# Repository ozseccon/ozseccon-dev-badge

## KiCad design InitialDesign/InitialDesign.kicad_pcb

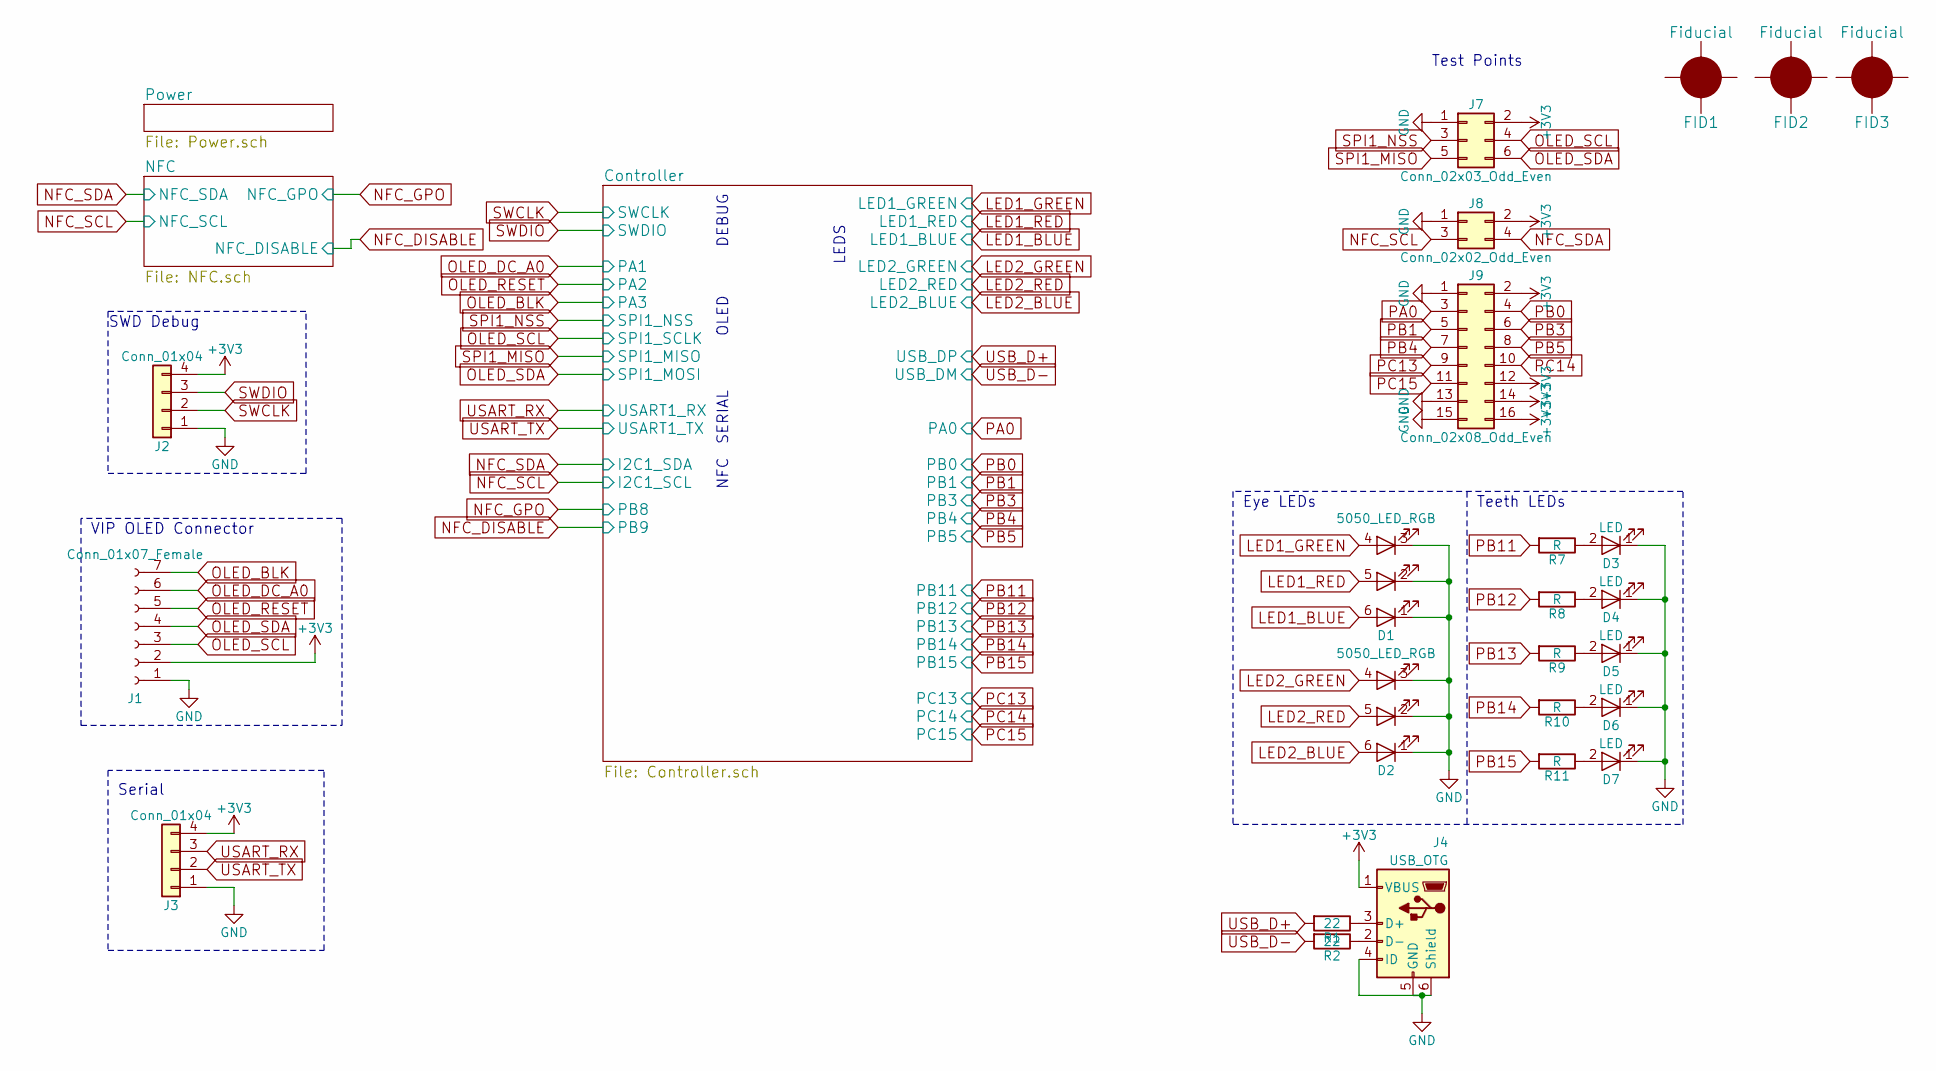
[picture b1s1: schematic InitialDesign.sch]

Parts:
D1, D2: 5050_LED_RGB; LED_RGB_5050-6
D3, D4, D5, D6, D7: LED; LED_1206
FID1, FID2, FID3: Fiducial; Fiducial_1.5mm_Dia_2.54mm_Outer_CopperTop
J1: Conn_01x07_Female; Socket_Strip_Straight_1x07_Pitch2.54mm
J2, J3: Conn_01x04; Pin_Header_Straight_1x04_Pitch2.54mm
J4: USB_OTG; USB_Micro-B
J7: Conn_02x03_Odd_Even; Pin_Header_Straight_2x03_Pitch2.54mm
J8: Conn_02x02_Odd_Even; Pin_Header_Straight_2x02_Pitch2.54mm
J9: Conn_02x08_Odd_Even; Pin_Header_Straight_2x08_Pitch2.54mm
R1, R2: 22; R_0805
R7, R8, R9, R10, R11: R; R_0805

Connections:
GND: D1.1 (K_BLUE), D1.2 (K_RED), D1.3 (K_GREEN), D2.1 (K_BLUE), D2.2 (K_RED), D2.3 (K_GREEN), D3.1 (K), D4.1 (K), D5.1 (K), D6.1 (K), D7.1 (K), J1.1, J2.1, J3.1, J4.4 (ID), J4.5 (GND), J4.6 (Shield), J7.1, J8.1, J9.1, J9.13, J9.15; also elsewhere on the board
LED1_BLUE: D1.6 (BLUE_A); also elsewhere on the board
LED1_GREEN: D1.4 (GREEN_A); also elsewhere on the board
LED1_RED: D1.5 (A_RED); also elsewhere on the board
LED2_BLUE: D2.6 (BLUE_A); also elsewhere on the board
LED2_GREEN: D2.4 (GREEN_A); also elsewhere on the board
LED2_RED: D2.5 (A_RED); also elsewhere on the board
NFC_SCL: J8.3; also elsewhere on the board
NFC_SDA: J8.4; also elsewhere on the board
unnamed: D3.2 (A), R7.1
unnamed: D4.2 (A), R8.1
unnamed: D5.2 (A), R9.1
unnamed: D6.2 (A), R10.1
unnamed: D7.2 (A), R11.1
unnamed: J4.2 (D-), R2.1
unnamed: J4.3 (D+), R1.1
OLED_BLK: J1.7; also elsewhere on the board
OLED_DC_A0: J1.6; also elsewhere on the board
OLED_RESET: J1.5; also elsewhere on the board
OLED_SCL: J1.3, J7.4; also elsewhere on the board
OLED_SDA: J1.4, J7.6; also elsewhere on the board
PA0: J9.3; also elsewhere on the board
PB0: J9.4; also elsewhere on the board
PB1: J9.5; also elsewhere on the board
PB3: J9.6; also elsewhere on the board
PB4: J9.7; also elsewhere on the board
PB5: J9.8; also elsewhere on the board
PB11: R7.2; also elsewhere on the board
PB12: R8.2; also elsewhere on the board
PB13: R9.2; also elsewhere on the board
PB14: R10.2; also elsewhere on the board
PB15: R11.2; also elsewhere on the board
PC13: J9.9; also elsewhere on the board
PC14: J9.10; also elsewhere on the board
PC15: J9.11; also elsewhere on the board
SPI1_MISO: J7.5; also elsewhere on the board
SPI1_NSS: J7.3; also elsewhere on the board
SWCLK: J2.2; also elsewhere on the board
SWDIO: J2.3; also elsewhere on the board
USART_RX: J3.3; also elsewhere on the board
USART_TX: J3.2; also elsewhere on the board
USB_D+: R1.2; also elsewhere on the board
USB_D-: R2.2; also elsewhere on the board

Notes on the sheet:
SWD Debug
VIP OLED Connector
Serial
DEBUG
OLED
SERIAL
NFC
LEDS
Teeth LEDs
Test Points
Eye LEDs

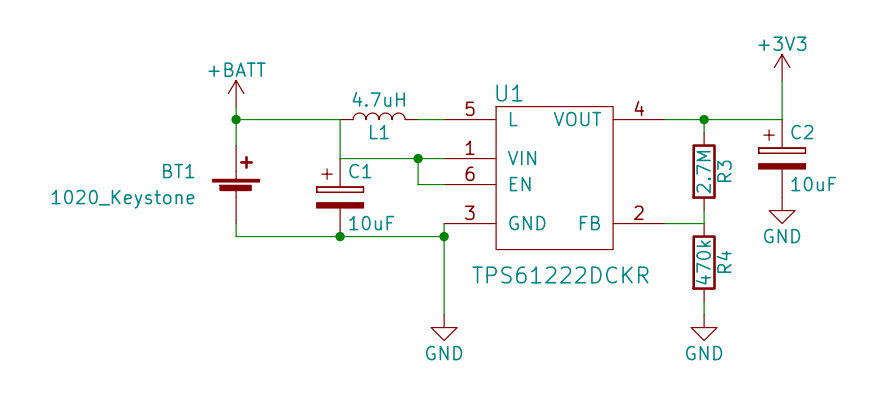
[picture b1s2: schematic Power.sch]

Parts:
BT1: 1020_Keystone; Keystone_2466_1xAAA
C1, C2: 10uF; CP_Elec_4x5.3
L1: 4.7uH; L_Taiyo-Yuden_NR-30xx
R3: 2.7M; R_0805
R4: 470k; R_0805
U1: TPS61222DCKR; SC-70-6

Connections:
+BATT: BT1.1 (+), C1.1, L1.1, U1.1 (VIN), U1.6 (EN)
GND: BT1.2 (-), C1.2, C2.2, R4.2, U1.3 (GND); also elsewhere on the board
unnamed: L1.2, U1.5 (L)
unnamed: R3.2, R4.1, U1.2 (FB)

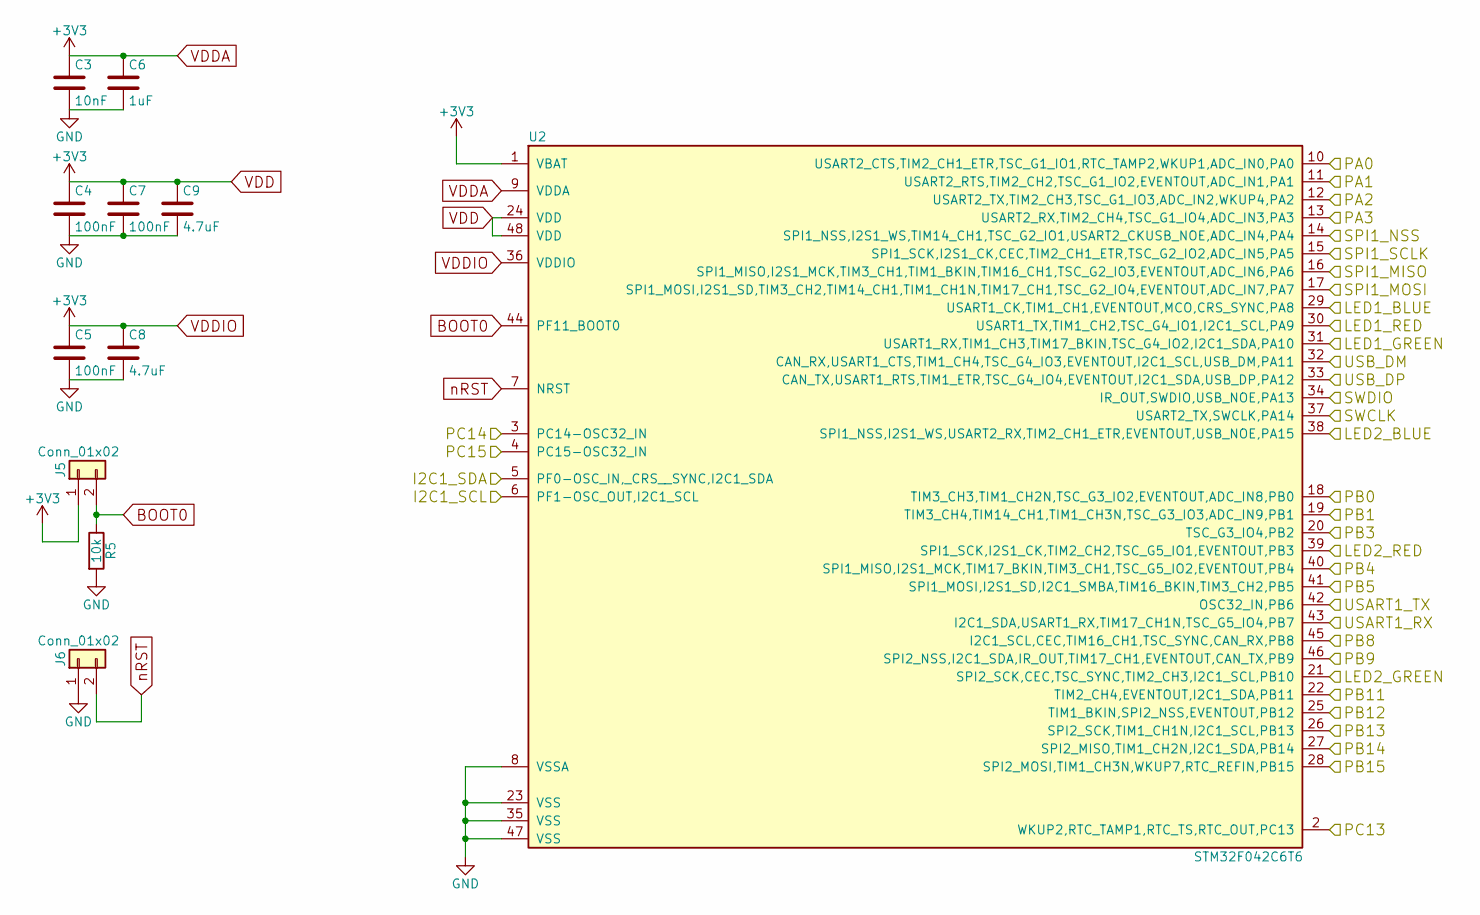
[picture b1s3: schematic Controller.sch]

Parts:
C3: 10nF; C_0805
C4, C5, C7: 100nF; C_0805
C6: 1uF; C_0805
C8, C9: 4.7uF; C_0805
J5, J6: Conn_01x02; Pin_Header_Straight_1x02_Pitch2.54mm
R5: 10k; R_0805
U2: STM32F042C6T6; LQFP-48_7x7mm_Pitch0.5mm

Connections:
BOOT0: J5.2, R5.1, U2.44 (PF11_BOOT0)
GND: C3.2, C4.2, C5.2, C6.2, C7.2, C8.2, C9.2, J6.1, R5.2, U2.8 (VSSA), U2.23 (VSS), U2.35 (VSS), U2.47 (VSS); also elsewhere on the board
LED1_BLUE: U2.29 (USART1_CK,TIM1_CH1,EVENTOUT,MCO,CRS_SYN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); also elsewhere on the board
LED1_GREEN: U2.31 (USART1_RX,TIM1_CH3,TIM17_BKIN,TSC_G4_IO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); also elsewhere on the board
LED1_RED: U2.30 (USART1_TX,TIM1_CH2,TSC_G4_IO1,I2C1_SCL,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); also elsewhere on the board
LED2_BLUE: U2.38 (SPI1_NSS,I2S1_WS,USART2_RX,TIM2_CH1_ETR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); also elsewhere on the board
LED2_GREEN: U2.21 (SPI2_SCK,CEC,TSC_SYNC,TIM2_CH3,I2C1_SCL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); also elsewhere on the board
LED2_RED: U2.39 (SPI1_SCK,I2S1_CK,TIM2_CH2,TSC_G5_IO1,EV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); also elsewhere on the board
NFC_DISABLE: U2.46 (SPI2_NSS,I2C1_SDA,IR_OUT,TIM17_CH1,EVEN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); also elsewhere on the board
NFC_GPO: U2.45 (I2C1_SCL,CEC,TIM16_CH1,TSC_SYNC,CAN_RX,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); also elsewhere on the board
NFC_SCL: U2.6 (PF1-OSC_OUT,I2C1_SCL); also elsewhere on the board
NFC_SDA: U2.5 (PF0-OSC_IN,_CRS__SYNC,I2C1_SDA); also elsewhere on the board
OLED_BLK: U2.13 (USART2_RX,TIM2_CH4,TSC_G1_IO4,ADC_IN3,P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); also elsewhere on the board
OLED_DC_A0: U2.11 (USART2_RTS,TIM2_CH2,TSC_G1_IO2,EVENTOUT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); also elsewhere on the board
OLED_RESET: U2.12 (USART2_TX,TIM2_CH3,TSC_G1_IO3,ADC_IN2,W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); also elsewhere on the board
OLED_SCL: U2.15 (SPI1_SCK,I2S1_CK,CEC,TIM2_CH1_ETR,TSC_G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); also elsewhere on the board
OLED_SDA: U2.17 (SPI1_MOSI,I2S1_SD,TIM3_CH2,TIM14_CH1,TI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); also elsewhere on the board
PA0: U2.10 (USART2_CTS,TIM2_CH1_ETR,TSC_G1_IO1,RTC_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); also elsewhere on the board
PB0: U2.18 (TIM3_CH3,TIM1_CH2N,TSC_G3_IO2,EVENTOUT,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); also elsewhere on the board
PB1: U2.19 (TIM3_CH4,TIM14_CH1,TIM1_CH3N,TSC_G3_IO3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); also elsewhere on the board
PB3: U2.20 (TSC_G3_IO4,PB2); also elsewhere on the board
PB4: U2.40 (SPI1_MISO,I2S1_MCK,TIM17_BKIN,TIM3_CH1,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); also elsewhere on the board
PB5: U2.41 (SPI1_MOSI,I2S1_SD,I2C1_SMBA,TIM16_BKIN,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); also elsewhere on the board
PB11: U2.22 (TIM2_CH4,EVENTOUT,I2C1_SDA,PB11); also elsewhere on the board
PB12: U2.25 (TIM1_BKIN,SPI2_NSS,EVENTOUT,PB12); also elsewhere on the board
PB13: U2.26 (SPI2_SCK,TIM1_CH1N,I2C1_SCL,PB13); also elsewhere on the board
PB14: U2.27 (SPI2_MISO,TIM1_CH2N,I2C1_SDA,PB14); also elsewhere on the board
PB15: U2.28 (SPI2_MOSI,TIM1_CH3N,WKUP7,RTC_REFIN,PB15); also elsewhere on the board
PC13: U2.2 (WKUP2,RTC_TAMP1,RTC_TS,RTC_OUT,PC13); also elsewhere on the board
PC14: U2.3 (PC14-OSC32_IN); also elsewhere on the board
PC15: U2.4 (PC15-OSC32_IN); also elsewhere on the board
SPI1_MISO: U2.16 (SPI1_MISO,I2S1_MCK,TIM3_CH1,TIM1_BKIN,T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); also elsewhere on the board
SPI1_NSS: U2.14 (SPI1_NSS,I2S1_WS,TIM14_CH1,TSC_G2_IO1,U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); also elsewhere on the board
SWCLK: U2.37 (USART2_TX,SWCLK,PA14); also elsewhere on the board
SWDIO: U2.34 (IR_OUT,SWDIO,USB_NOE,PA13); also elsewhere on the board
USART_RX: U2.43 (I2C1_SDA,USART1_RX,TIM17_CH1N,TSC_G5_IO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); also elsewhere on the board
USART_TX: U2.42 (OSC32_IN,PB6); also elsewhere on the board
USB_D+: U2.33 (CAN_TX,USART1_RTS,TIM1_ETR,TSC_G4_IO4,E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); also elsewhere on the board
USB_D-: U2.32 (CAN_RX,USART1_CTS,TIM1_CH4,TSC_G4_IO3,E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); also elsewhere on the board
nRST: J6.2, U2.7 (NRST)

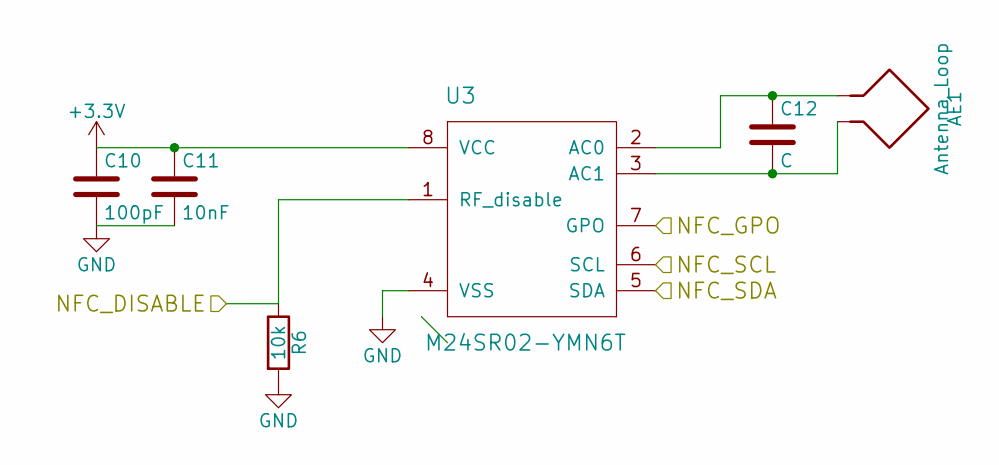
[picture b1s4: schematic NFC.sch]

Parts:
AE1: Antenna_Loop; NFC_Antenna
C10: 100pF; C_0805
C11: 10nF; C_0805
C12: C; C_0805
R6: 10k; R_0805
U3: M24SR02-YMN6T; SO-8_5.3x6.2mm_Pitch1.27mm

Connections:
GND: C10.2, C11.2, R6.2, U3.4 (VSS); also elsewhere on the board
NFC_DISABLE: R6.1, U3.1 (RF_disable); also elsewhere on the board
NFC_GPO: U3.7 (GPO); also elsewhere on the board
NFC_SCL: U3.6 (SCL); also elsewhere on the board
NFC_SDA: U3.5 (SDA); also elsewhere on the board
unnamed: AE1.1, C12.1, U3.2 (AC0)
unnamed: AE1.2, C12.2, U3.3 (AC1)

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
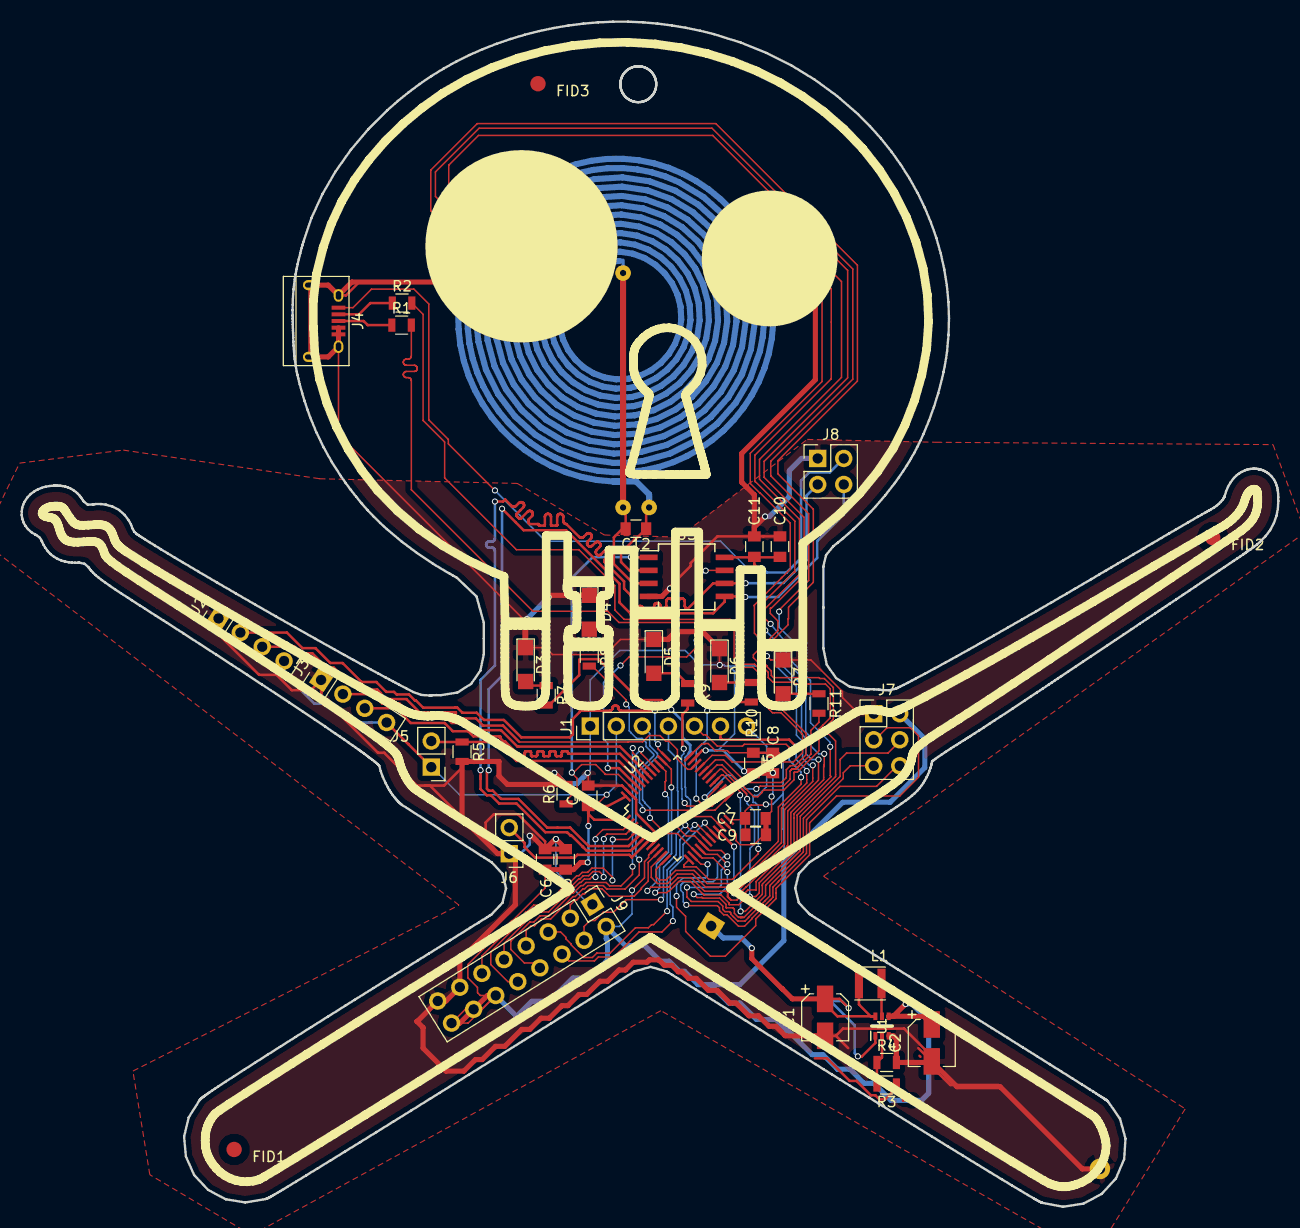
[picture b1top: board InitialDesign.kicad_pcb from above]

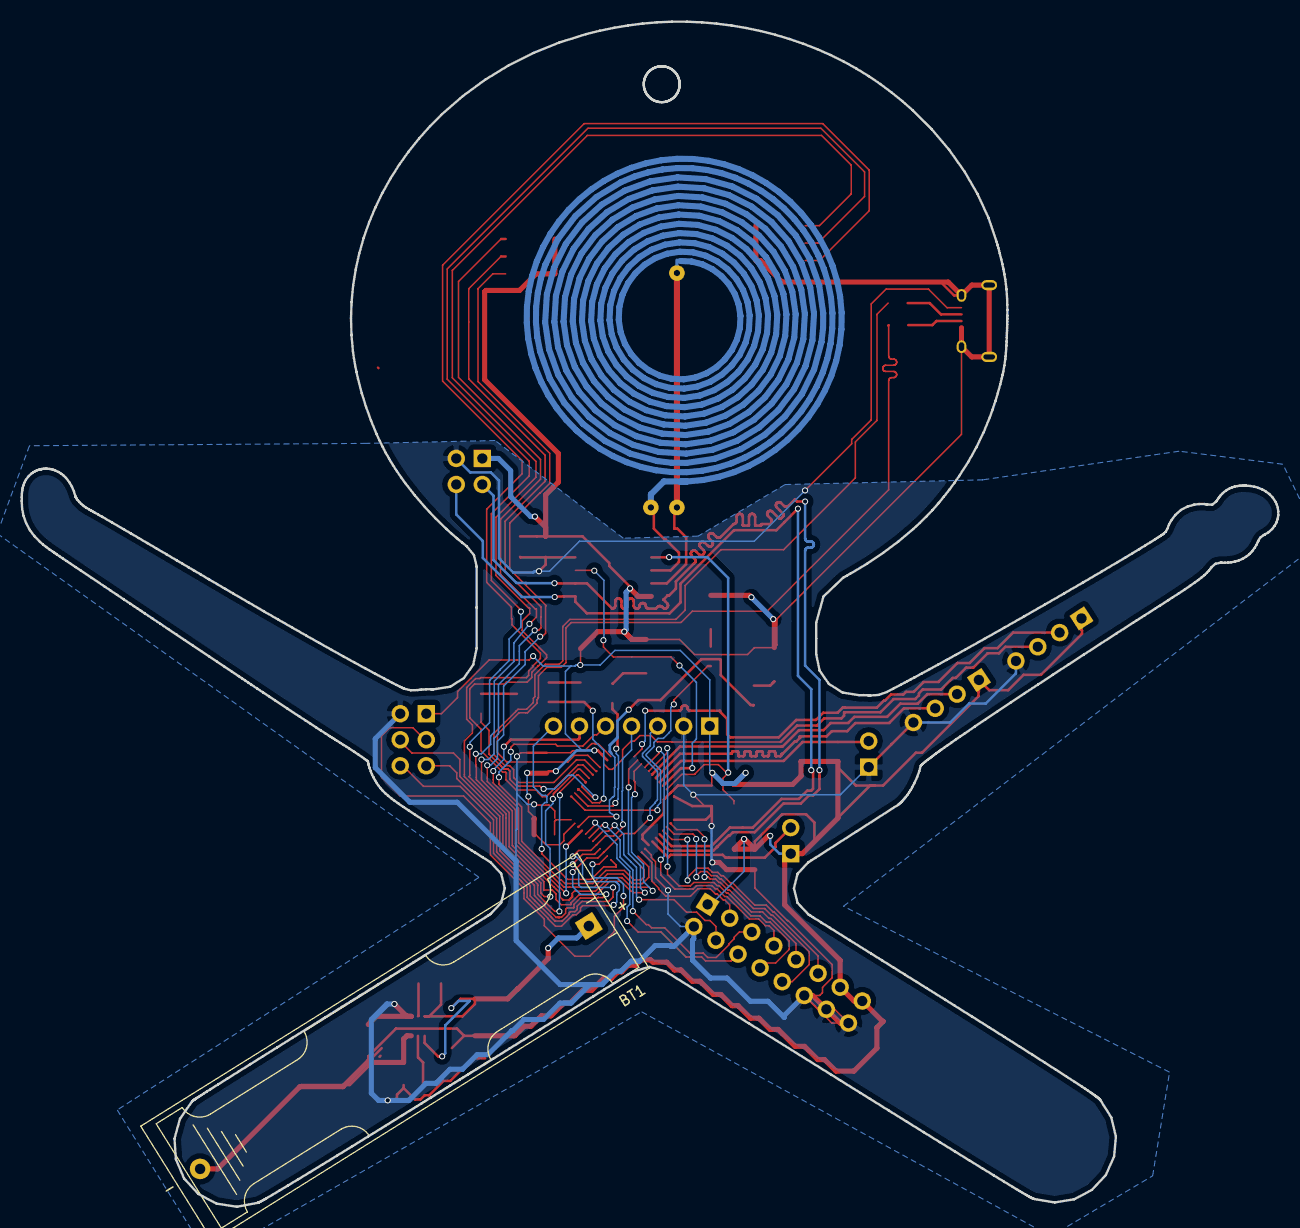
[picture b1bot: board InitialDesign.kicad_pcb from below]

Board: 2 copper layers, 122.5 x 115.6 mm, 49 parts (2 on the bottom side), 53 nets.

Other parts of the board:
skully: G***; Skully

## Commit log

2018-01-12 Schematic and Layout commenced
2018-01-14 Initial proto done
